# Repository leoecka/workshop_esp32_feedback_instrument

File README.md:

# Workshop on Feedback Instrument with Embedded Systems

An acoustic and digital feedback instrument based on an **ESP32 DevKit**, developed for the workshop on DIY feedback instruments. The system closes an audio loop through the physical space via microphone, digital signal processing (DSP), and speaker/line-out—complemented by a potentiometer and capacitive touch contacts on the ESP32.

---

## 1. Hardware & Assembly

The PCB connects a **30-pin ESP32 DevKit** to a digital I2S microphone, an audio output stage, a potentiometer, and optional analog inputs.

### Components & Connectors
* **Microcontroller:** ESP32 DevKit (30-pin version; align the antenna end over the keep-out zone on the PCB).
* **Microphone (`J2`):** **INMP441** I2S MEMS microphone (mounted directly or via Dupont wires; `L/R` is tied to `GND` for the left channel).
* **Audio Output (`J1` / `J3`):** Both headers are wired in parallel to the same I2S lines and can be populated individually or simultaneously:
  * **`J1` (AMP):** **MAX98357A** Class-D mono amplifier for driving a speaker directly.
  * **`J3` (LINE OUT):** **PCM5102A** stereo DAC for line-out / headphones.
    > **Important:** On the back of the PCM5102A module, the solder jumpers must be set to `FLT = L`, `DEMP = L`, `XSMT = H`, and `FMT = L`—otherwise the module will remain muted.
* **Controls:**
  * **`RV1`:** 10k linear potentiometer (9 mm, e.g., Alps RK09K, Bourns PTV09, or Alpha).
  * **Capacitive Touch Pins:** Solder pads **`D4`** (`GPIO 4`) and **`D32`** (`GPIO 32`) directly on the ESP32 board act as touch-sensitive buttons in several sketches.
* **Expansion (`J4` – Piezo):** 4-pin header (`3V3`, `GND`, `A1`, `A2`) with 1k protection resistors—e.g., for a piezo preamp, line-in, or additional potentiometers.

### On-Board Jumpers
* **`JP1` (AMP Left Only):** Bridged = amplifier plays left channel only | Open = mix of left and right channels.
* **`JP2` (AMP Gain):** Bridge `1–2` = 12 dB | Open = 9 dB | Bridge `2–3` = 6 dB.

### Pinout (ESP32 DevKit)
| Function | GPIO | Pin / Notes |
| :--- | :--- | :--- |
| **I2S BCLK** | `GPIO 26` | Shared Bit-Clock (Mic & Out) |
| **I2S WS / LRC** | `GPIO 25` | Shared Word-Select (Mic & Out) |
| **I2S DOUT** | `GPIO 22` | Audio Data to AMP / Line-Out |
| **I2S MIC IN** | `GPIO 35` | Audio Data from INMP441 |
| **Potentiometer** | `GPIO 34` | Analog Input (ADC1) |
| **Touch 1** | `GPIO 4` | Solder pad `D4` on the DevKit |
| **Touch 2** | `GPIO 32` | Solder pad `D32` on the DevKit |
| **Piezo A1 / A2** | `GPIO 36` / `39` | Analog expansion inputs |
| **Status LED** | `GPIO 2` | Onboard blue LED of the ESP32 |

---

## 2. Software Setup & Installation

All sketches are written for the **Arduino IDE** and require **Arduino-ESP32 Core version 3.x** (based on ESP-IDF 5).

### Step 1: Install Arduino IDE & ESP32 Board Package
1. Download and install the latest **Arduino IDE (2.x)**.
2. Open **Preferences / Settings** (*File → Preferences* on Windows/Linux or *Arduino IDE → Settings* on macOS).
3. Under **Additional Boards Manager URLs**, add the following URL:
   ```text
   [https://espressif.github.io/arduino-esp32/package_esp32_index.json](https://espressif.github.io/arduino-esp32/package_esp32_index.json)
   ```
4. Alternatively, open the **Boards Manager** on the left sidebar, search for **`esp32`**, and install **`esp32` by Espressif Systems** (version **3.x** or newer).

### Step 2: Select Board
Go to **Tools → Board → esp32** and select **`ESP32 Dev Module`**. *(Default settings for Upload Speed, Flash Frequency, etc. can be left unchanged.)*

### Step 3: USB Drivers & Port Selection by OS
Connect the ESP32 to your computer using a **USB data cable** (*note: some USB cables are power-only and will not transmit data*). Select the port under **Tools → Port**:

* **Windows:**
  * The port appears as **`COMx`** (e.g., `COM3`, `COM4`).
  * **Tip:** Open the **Windows Device Manager** under *Ports (COM & LPT)* to see which COM port number appears when plugging in the board.
  * **Drivers:** If no COM port shows up or a yellow warning icon appears, install the USB-to-UART driver matching the chip on your DevKit: either **Silicon Labs CP210x** (square chip) or **WCH CH340 / CH341** (rectangular chip).
* **macOS:**
  * The port appears as `/dev/cu.usbserial-...` or `/dev/cu.SLAB_USBtoUART` (on recent macOS versions, drivers for CP210x and CH340 are usually built in; if not, install the corresponding driver from Silicon Labs or WCH).
* **Linux:**
  * The port appears as `/dev/ttyUSB0` (or `ttyACM0`).
  * If you encounter a *Permission denied* error during upload, add your user to the `dialout` group and log out/in again:
```bash
sudo usermod -a -G dialout $USER
```

### Step 4: Upload & Serial Monitor
1. Open any sketch from this repository and click **Upload**. *(If the upload hangs at `"Connecting..."`, press and hold the **BOOT** button on the ESP32 until flashing begins.)*
2. Open the **Serial Monitor** (**Tools → Serial Monitor**) and set the baud rate in the bottom-right corner to **`115200`**. It displays live telemetry including audio levels, filter cutoff frequencies, touch states, and system status.

---

## 3. Included Sketches (Sound Engines)

* **`FB_Pure`:** Acoustic feedback governed by a "Modal States" behavior. System gain ramps up until the loop begins to sing; as resonance builds, the system "fatigues," drops down, rests, and grows again. The potentiometer controls the low-pass filter cutoff (`60–2000 Hz`).
* **`Self-FM`:** A sawtooth oscillator modulates its own pitch via the microphone picking up the acoustic room signal (frequency and ring modulation). Lower half of the pot controls volume and filter at `100 Hz`; upper half sweeps pitch up to `800 Hz`.
* **`Self-FM Touch`:** Extended version of *Self-FM*. Using touch pins **`D32`** (next) and **`D4`** (previous), the potentiometer cycles through 4 parameter pages with soft-takeover (pickup) logic: `1: JOURNEY` (level/pitch), `2: SHAPE` (sawtooth to square), `3: FM` depth, and `4: RING` modulation.
* **`Fireflies Pentatonic`:** Coupled oscillators interacting across the room. Each board plays notes from an A-minor pentatonic scale and accelerates its internal clock whenever it hears neighboring boards through the microphone (swarm synchronization). The pot controls pitch, envelope character (pad to percussive), and tempo.
* **`Tape Loop`:** Sound-on-sound tape looper running in the ESP32's RAM. Pot = feedback/erase multiplier; hold **`D4`** = record; hold **`D32`** = pot controls playback speed (`0.5x` to `2.0x`).
* **`FB_Pure_touch`:** Combines *Modal Feedback* with a waveform-aligned granular pitch shifter (WSOLA) and a tape delay directly inside the feedback loop. Hold **`D4`** = pitch (`0.9–1.1`), hold **`D32`** = delay time (`0–1000 ms`), hold **both** = reset pitch to `1.0`.
* **`Piezo / Line Passthrough`:** Low-latency audio passthrough (`50 kHz` sample rate to push switching noise above the audible range) for analog input **`A1`** (`GPIO 36`), featuring a median filter, oversampling, high-pass filter, and spectral noise gate *(requires an external preamp / voltage divider at the input)*.

---

## 4. License

This repository uses dual licensing to properly cover both hardware designs and firmware code:

* **Software & Firmware (`.ino` sketches):** Licensed under the **Apache License 2.0** — see [`LICENSE`](LICENSE). You may freely use, modify, and distribute the code, provided you retain copyright notices and clearly state any modifications made to the files.
* **Hardware (PCB schematics, layout, Gerber files):** Licensed under the **CERN Open Hardware Licence Version 2 – Weakly Reciprocal (`CERN-OHL-W-2.0`)** — see [`LICENSE-HARDWARE`](LICENSE-HARDWARE). You are free to manufacture, modify, and distribute the hardware, provided you give attribution, document any modifications, and share modified hardware design files under the same license.

---

## 5. Notes

* Both the firmware code and the PCB design were developed with AI assistance.

Copyright © 2026 Leon Eckard

*Funded by Musikfonds e.V. by means of the Federal Government Commissioner for Culture and the Media.*

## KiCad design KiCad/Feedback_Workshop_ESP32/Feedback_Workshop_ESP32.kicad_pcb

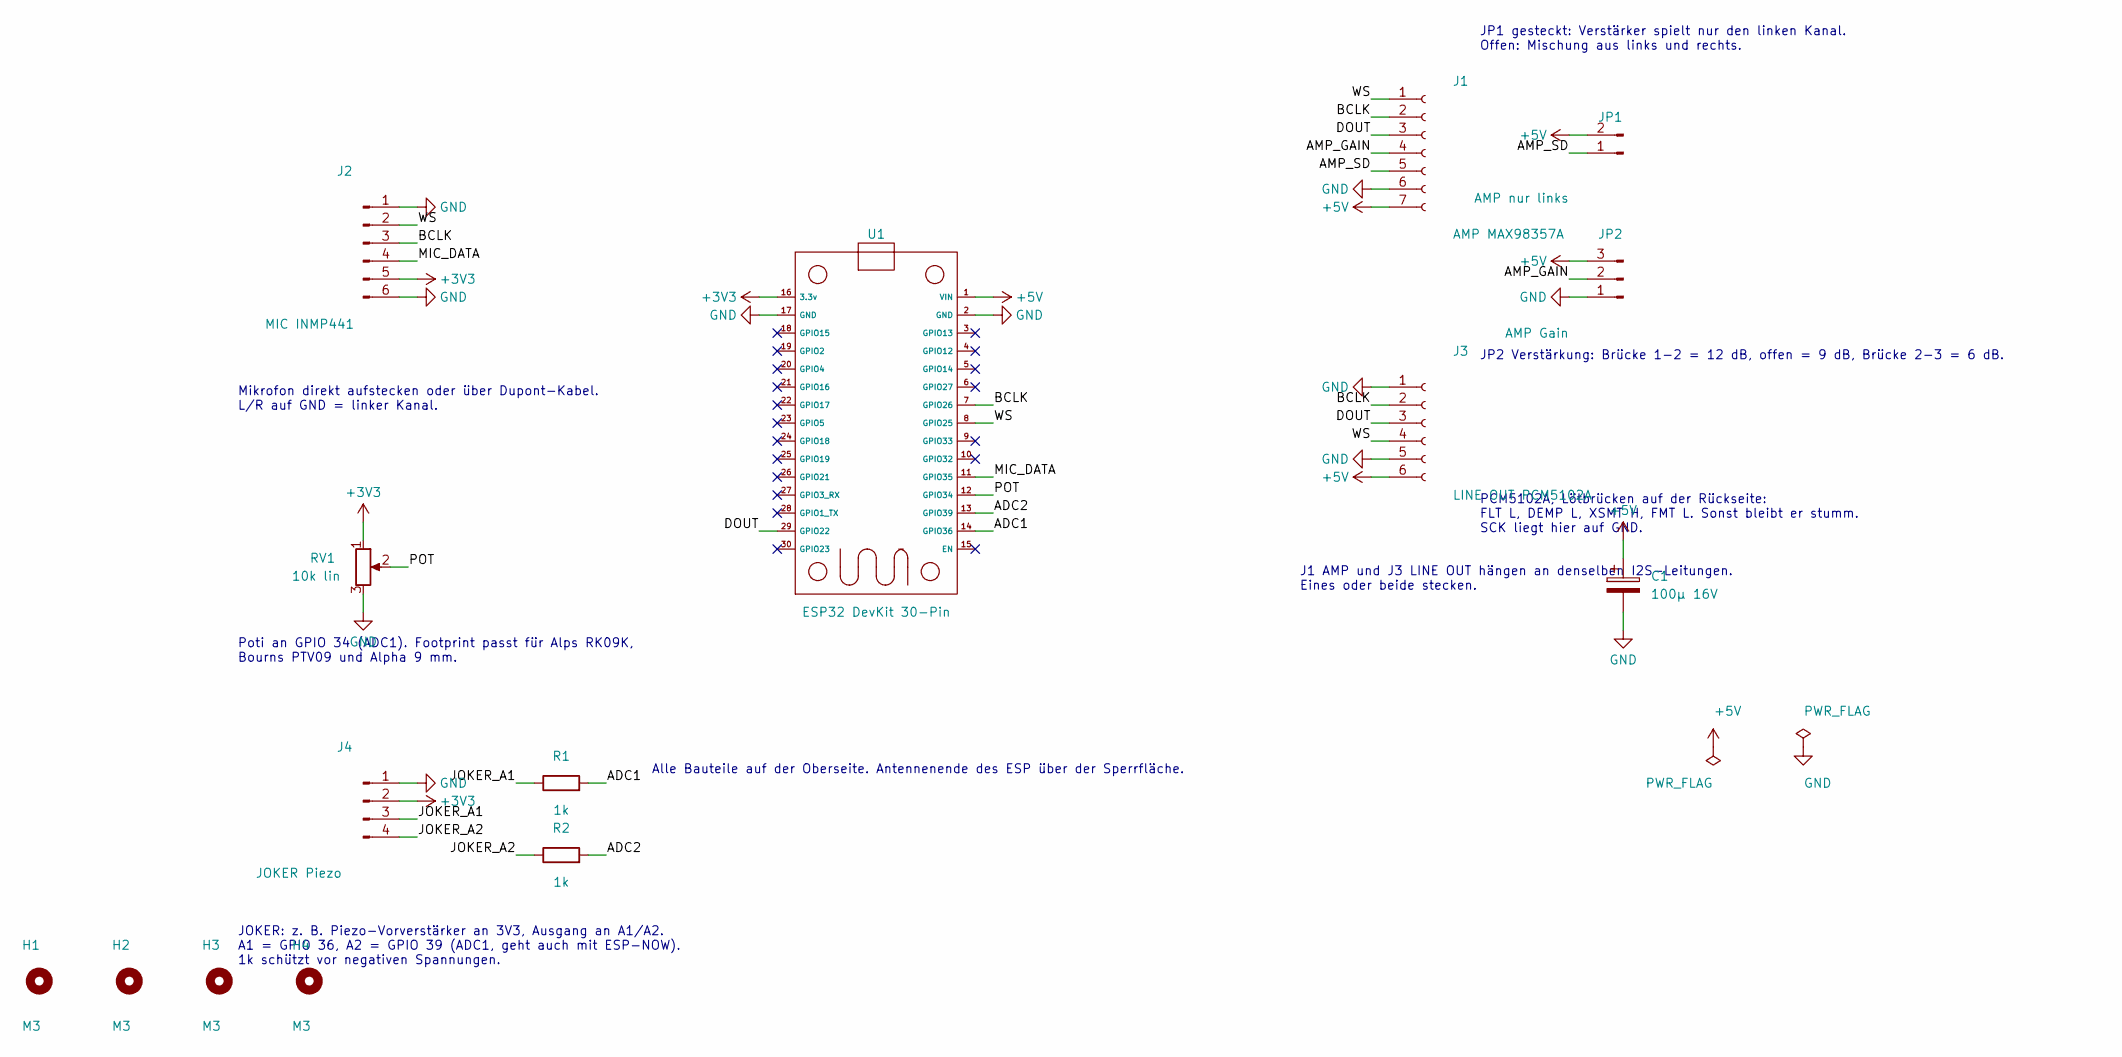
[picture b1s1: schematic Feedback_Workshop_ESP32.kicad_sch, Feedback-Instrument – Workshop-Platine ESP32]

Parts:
C1: 100µ 16V; CP_Radial_D6.3mm_P2.50mm
H1, H2, H3, H4: M3; MountingHole_3.2mm_M3
J1: AMP MAX98357A; PinSocket_1x07_P2.54mm_Vertical
J2: MIC INMP441; INMP441_Module_2x3
J3: LINE OUT PCM5102A; PinSocket_1x06_P2.54mm_Vertical
J4: JOKER Piezo; PinHeader_1x04_P2.54mm_Vertical
JP1: AMP nur links; PinHeader_1x02_P2.54mm_Vertical
JP2: AMP Gain; PinHeader_1x03_P2.54mm_Vertical
R1, R2: 1k; R_Axial_DIN0207_L6.3mm_D2.5mm_P7.62mm_Horizontal
RV1: 10k lin; Poti_9mm_Universal
U1: ESP32 DevKit 30-Pin; ESP32_DevKit_30pin

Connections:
+3V3: J2.5 (VDD), J4.2, RV1.1, U1.16 (3.3v)
+5V: C1.1, J1.7, J3.6, JP1.2, JP2.3, U1.1 (VIN)
/ADC1: R1.2, U1.14 (GPIO36)
/ADC2: R2.2, U1.13 (GPIO39)
/AMP_GAIN: J1.4, JP2.2
/AMP_SD: J1.5, JP1.1
/BCLK: J1.2, J2.3 (SCK), J3.2, U1.7 (GPIO26)
/DOUT: J1.3, J3.3, U1.29 (GPIO22)
/JOKER_A1: J4.3, R1.1
/JOKER_A2: J4.4, R2.1
/MIC_DATA: J2.4 (SD), U1.11 (GPIO35)
/POT: RV1.2, U1.12 (GPIO34)
/WS: J1.1, J2.2 (WS), J3.4, U1.8 (GPIO25)
GND: C1.2, J1.6, J2.1 (LR), J2.6 (GND), J3.1, J3.5, J4.1, JP2.1, RV1.3, U1.2 (GND), U1.17 (GND)

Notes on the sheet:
Mikrofon direkt aufstecken oder über Dupont-Kabel. L/R auf GND = linker Kanal.
Poti an GPIO 34 (ADC1). Footprint passt für Alps RK09K, Bourns PTV09 und Alpha 9 mm.
JP1 gesteckt: Verstärker spielt nur den linken Kanal. Offen: Mischung aus links und rechts.
JOKER: z. B. Piezo-Vorverstärker an 3V3, Ausgang an A1/A2. A1 = GPIO 36, A2 = GPIO 39 (ADC1, geht auch mit ESP-NOW). 1k schützt vor negativen Spannungen.
Alle Bauteile auf der Oberseite. Antennenende des ESP über der Sperrfläche.
JP2 Verstärkung: Brücke 1-2 = 12 dB, offen = 9 dB, Brücke 2-3 = 6 dB.
PCM5102A, Lötbrücken auf der Rückseite: FLT L, DEMP L, XSMT H, FMT L. Sonst bleibt er stumm. SCK liegt hier auf GND.
J1 AMP und J3 LINE OUT hängen an denselben I2S-Leitungen. Eines oder beide stecken.

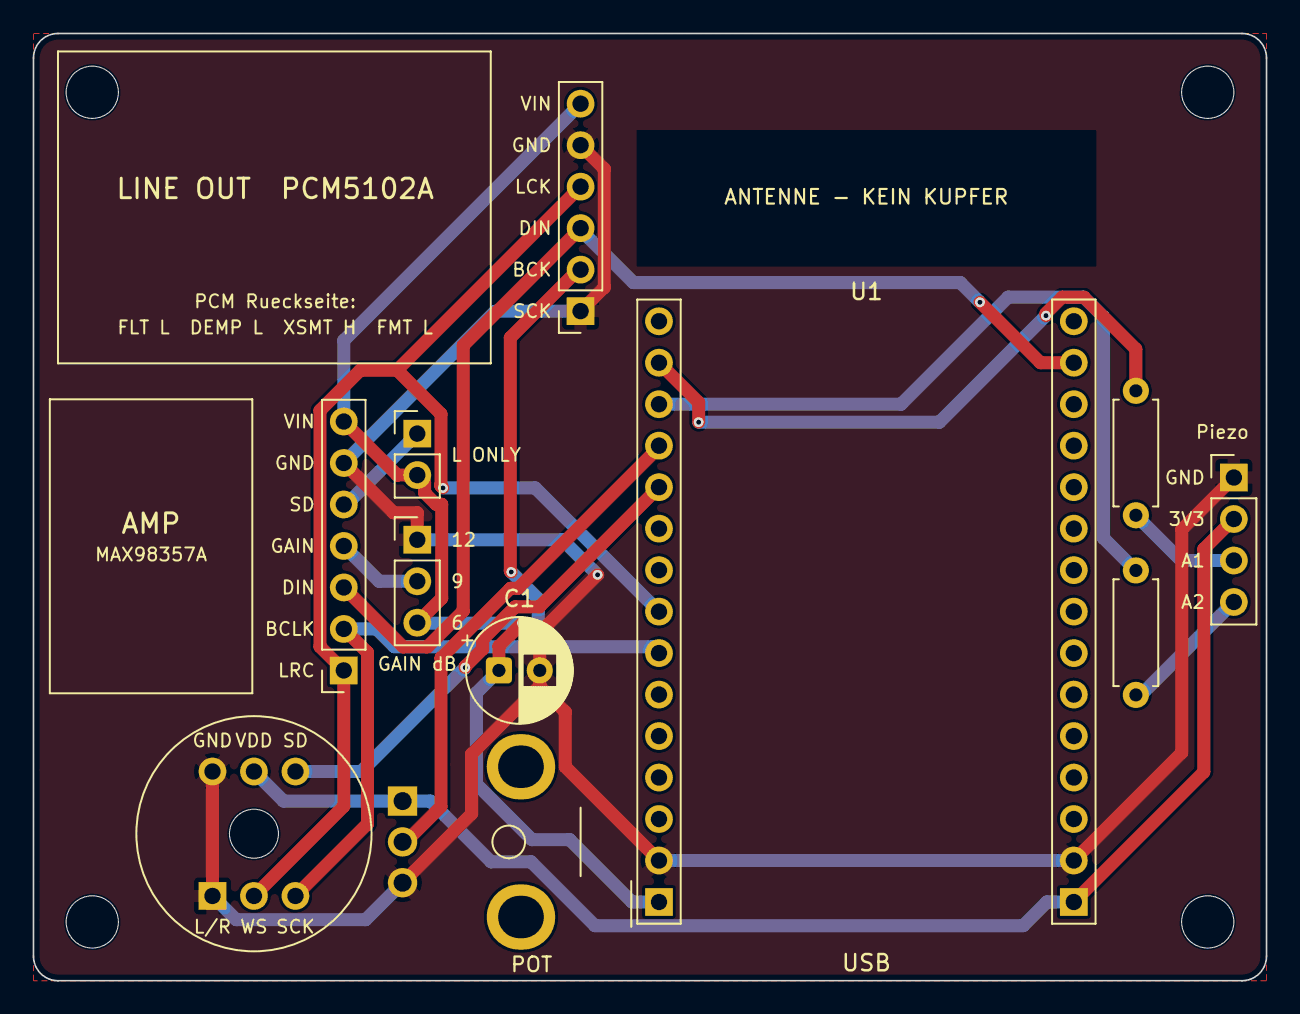
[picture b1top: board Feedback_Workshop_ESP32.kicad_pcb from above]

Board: 2 copper layers, 75.5 x 58.0 mm, 15 parts (0 on the bottom side), 14 nets.

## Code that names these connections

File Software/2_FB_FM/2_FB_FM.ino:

// =====================================================================
//  SELF-FM – a sawtooth that modulates itself through the air
//  Feedback workshop board v2 · Leon Eckard 2026
//
//  The microphone hears its own speaker, and exactly this signal bends
//  the pitch of the sawtooth: frequency modulation with itself, through
//  room, distance and housing. Every movement in the room changes the sound.
//
//  Pot (fully down = 0):
//    0          silent
//    0 .. 1/2   100 Hz, slowly gets louder, lowpass opens 120 -> 2000 Hz
//    1/2 .. 1   pitch rises from 100 Hz up to PITCH_MAX, filter follows
//
//  Arduino-ESP32 3.x (ESP-IDF 5), board "ESP32 Dev Module".
// =====================================================================

#include <Arduino.h>
#include <driver/i2s_std.h>
#include <math.h>

// ---------- Pins of board v2 ----------
#define PIN_BCLK  26
#define PIN_WS    25
#define PIN_DOUT  22   // to AMP and LINE OUT
#define PIN_MIC   35   // data from the INMP441
#define PIN_POT   34

// ---------- Things to play with ----------
const float FM_DEPTH  = 0.5f;    // 0.10 = the mic bends the pitch by up to ±10 %
const float RING      = 0.2f;    // 0..1: also multiply by the mic signal (ring modulation)
const float MIC_GAIN  = 50.0f;   // how much the mic is amplified before modulating
const float BASE_HZ   = 100.0f;
const float PITCH_MAX = 800.0f;  // highest pitch with the pot fully up
const float FILTER_Q  = 1.2f;
const float VOLUME    = 0.4f;
const bool  POT_INVERT = true;   // on this board, fully down reads the highest value

// ---------- Audio ----------
const int SR = 44100;
const int N  = 128;              // frames per block, about 2.9 ms
int32_t rxBuf[N * 2], txBuf[N * 2];
i2s_chan_handle_t txChan, rxChan;

float sawPhase = 0;
float potS = 0;                  // smoothed pot
float ampNow = 0;                // volume, smoothed per sample
float ic1 = 0, ic2 = 0;          // filter state
float hpX = 0, hpY = 0;          // DC blocker state
float micLvl = 0;
uint32_t blockCount = 0;

// sawtooth correction (PolyBLEP) so it aliases less
static inline float polyblep(float t, float dt) {
  if (t < dt)        { t /= dt;             return t + t - t * t - 1.0f; }
  if (t > 1.0f - dt) { t = (t - 1.0f) / dt; return t * t + t + t + 1.0f; }
  return 0.0f;
}

void setupI2S() {
  i2s_chan_config_t chanCfg = I2S_CHANNEL_DEFAULT_CONFIG(I2S_NUM_0, I2S_ROLE_MASTER);
  chanCfg.dma_desc_num  = 4;
  chanCfg.dma_frame_num = N;
  chanCfg.auto_clear    = true;
  // one port, two channels: send and receive share the same clocks
  ESP_ERROR_CHECK(i2s_new_channel(&chanCfg, &txChan, &rxChan));
  i2s_std_config_t stdCfg = {
    .clk_cfg  = I2S_STD_CLK_DEFAULT_CONFIG(SR),
    .slot_cfg = I2S_STD_PHILIPS_SLOT_DEFAULT_CONFIG(I2S_DATA_BIT_WIDTH_32BIT, I2S_SLOT_MODE_STEREO),
    .gpio_cfg = {
      .mclk = I2S_GPIO_UNUSED,
      .bclk = (gpio_num_t)PIN_BCLK,
      .ws   = (gpio_num_t)PIN_WS,
      .dout = (gpio_num_t)PIN_DOUT,
      .din  = (gpio_num_t)PIN_MIC,
      .invert_flags = { .mclk_inv = false, .bclk_inv = false, .ws_inv = false },
    },
  };
  ESP_ERROR_CHECK(i2s_channel_init_std_mode(txChan, &stdCfg));
  ESP_ERROR_CHECK(i2s_channel_init_std_mode(rxChan, &stdCfg));
  ESP_ERROR_CHECK(i2s_channel_enable(txChan));
  ESP_ERROR_CHECK(i2s_channel_enable(rxChan));
}

void setup() {
  Serial.begin(115200);
  analogReadResolution(12);
  setupI2S();
  Serial.println("Self-FM ready.");
}

void loop() {
  // reading one block of microphone data also sets the timing
  size_t got = 0;
  i2s_channel_read(rxChan, rxBuf, sizeof(rxBuf), &got, portMAX_DELAY);

  // ---- Pot: 0 = fully down ----
  float p = analogRead(PIN_POT) / 4095.0f;
  if (POT_INVERT) p = 1.0f - p;
  potS += (p - potS) * 0.08f;
  float q = potS < 0.01f ? 0.0f : potS;          // really silent at the bottom

  // ---- The pot journey ----
  float ampTarget, freq, fc;
  if (q < 0.5f) {
    float h = q / 0.5f;                          // 0..1 in the lower half
    ampTarget = h * h;                           // slowly louder
    freq = BASE_HZ;
    fc = 120.0f * powf(2000.0f / 120.0f, h);     // filter opens exponentially
  } else {
    float h = (q - 0.5f) / 0.5f;                 // 0..1 in the upper half
    ampTarget = 1.0f;
    freq = BASE_HZ * powf(PITCH_MAX / BASE_HZ, h);
    fc = 2000.0f * (freq / BASE_HZ);             // filter follows the pitch
  }
  if (fc > 9000.0f) fc = 9000.0f;

  // lowpass coefficients, once per block (TPT state variable filter)
  float g  = tanf(PI * fc / SR);
  float k  = 1.0f / FILTER_Q;
  float a1 = 1.0f / (1.0f + g * (g + k));
  float a2 = g * a1, a3 = g * a2;
  float ampStep = (ampTarget - ampNow) / N;      // glide across the block, no clicks

  for (int i = 0; i < N; i++) {
    // ---- Mic: remove DC, soft-limit to ±1 ----
    float x = (rxBuf[2 * i] >> 8) / 8388608.0f; // 24 bit in the top of a 32 bit word
    float y = x - hpX + 0.995f * hpY;  hpX = x; hpY = y;
    float m = tanhf(y * MIC_GAIN);
    float r = fabsf(m);
    micLvl += (r - micLvl) * 0.001f;

    // ---- FM: the mic bends the pitch ----
    float dt = freq * (1.0f + FM_DEPTH * m) / SR;
    float saw = 2.0f * sawPhase - 1.0f - polyblep(sawPhase, dt);
    sawPhase += dt;
    if (sawPhase >= 1.0f) sawPhase -= 1.0f;

    // ---- optionally also multiply (ring modulation) ----
    saw *= (1.0f - RING) + RING * m;

    // ---- Lowpass ----
    float v3 = saw - ic2;
    float v1 = a1 * ic1 + a2 * v3;
    float v2 = ic2 + a2 * ic1 + a3 * v3;
    ic1 = 2.0f * v1 - ic1;
    ic2 = 2.0f * v2 - ic2;

    ampNow += ampStep;
    float out = v2 * ampNow * VOLUME;
    if (out > 1.0f) out = 1.0f; else if (out < -1.0f) out = -1.0f;
    int32_t s = (int32_t)(out * 2147483000.0f);
    txBuf[2 * i] = s;                            // left
    txBuf[2 * i + 1] = s;                        // right, same signal
  }

  size_t written = 0;
  i2s_channel_write(txChan, txBuf, sizeof(txBuf), &written, portMAX_DELAY);

  // ---- Monitor, twice per second (115200 baud) ----
  if (++blockCount % 172 == 0) {
    Serial.printf("pot %.2f | %5.1f Hz | filter %5.0f Hz | volume %.2f | mic %.2f\n",
                  q, freq, fc, ampNow, micLvl);
  }
}
